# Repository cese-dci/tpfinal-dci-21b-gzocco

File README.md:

## Trabajo práctico final de la asignatura DCI ##
Este repositorio contiene el trabajo práctico final para la asignatura de Diseño de Circuitos Impresos de la carrera de posgrado de FIUBA.

* **Autor:** Gustavo Zocco
* **Revisor:** Agustín Curcio Berardi
* **Docente:** Diego Brengui
* **Título corto del trabajo:** Réplica Giroscopio L3GD20H.
* **Descripción:**  Réplica del módulo giroscopio de 3 ejes con el CI L3GD20H.

<p align="center">
    <br>
    <b>Figura 1</b>. Vista de frente de la placa adaptada. 
</p>

<p align="center">
    <br>
    <b>Figura 2</b>. Vista en perspectiva 3d de la placa adaptada. 
</p>

## Adaptaciones realizadas al replicar la placa ##

En este trabajo se realizaron adaptaciones sobre la placa propuesta a los efectos de satisfacer los requerimientos establecidos, como se detalla a cantinuación:

- Se agregó un tercer fiducial.
- Se agregaron las referencias a los componentes que no las tenían en el diseño original.
- Como consecuencia de documentar las referencias la placa tiene 21 mm de alto (2 mm más que la original) y 37 mm de ancho (6.5 mm más que la original).
- Se agregó plano de tierra de GND en la cara superior de la placa.

## Licencia de este trabajo ##
CERN Open Hardware License (OHL)
Ver la sección "What license should I use?": https://www.oshwa.org/faq/

## Estructura ##

El presente trabajo contempla la siguiente estructura.

* doc: Toda la información sobre el circuito.
  * Notas de aplicación.
  * Esquemático.
  * Fotos de los prototipos.
* info: Toda la iformación recolectada, principalmente de terceros, como por ejemplo:
  * Hojas de datos.
  * Notas de aplicación.
  * Info de productos comerciales.
  * Info en internet.
* pcb: Archivos de diseño esquemático y pcb.

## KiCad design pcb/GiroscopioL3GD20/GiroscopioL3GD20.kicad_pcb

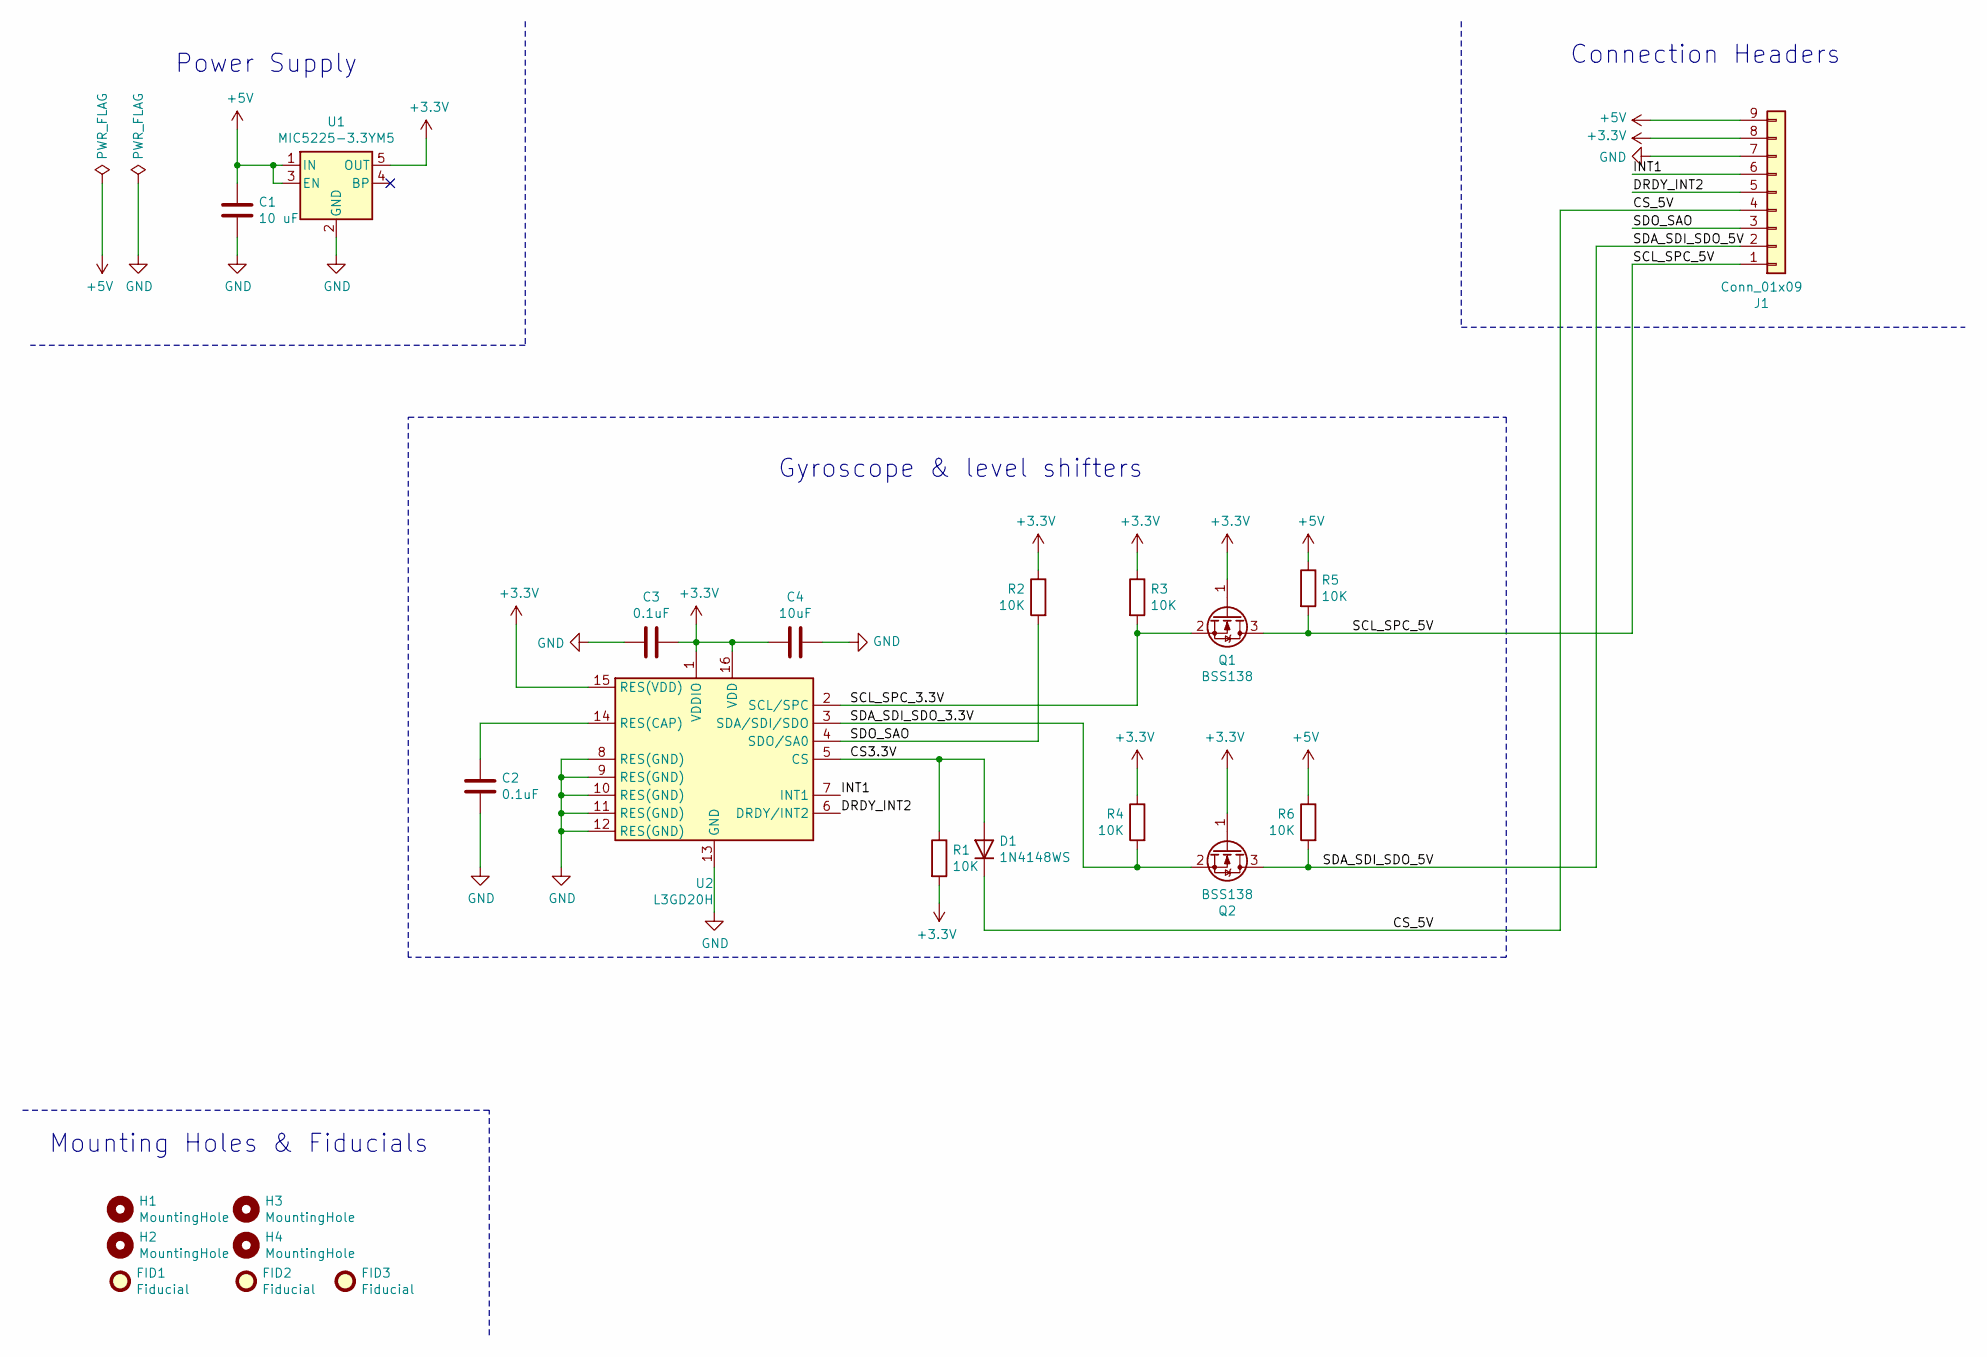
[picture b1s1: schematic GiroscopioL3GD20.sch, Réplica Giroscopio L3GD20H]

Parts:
C1: 10 uF; C_0805_2012Metric_Pad1.18x1.45mm_HandSolder
C2, C3: 0.1uF; C_0805_2012Metric_Pad1.18x1.45mm_HandSolder
C4: 10uF; C_0805_2012Metric_Pad1.18x1.45mm_HandSolder
D1: 1N4148WS; D_SOD-323
FID1, FID2, FID3: Fiducial; Fiducial_1mm_Mask2mm
H1, H2, H3, H4: MountingHole; MountingHole_2.5mm_Pad_TopBottom
J1: Conn_01x09; PinHeader_1x09_P2.54mm_Vertical
Q1: BSS138; SOT-23; Digi-Key PN BSS138-DIE-ND
Q2: BSS138; SOT-23; Digi-Key PN BSS138TR-ND
R1, R2, R3, R4, R5, R6: 10K; R_0805_2012Metric_Pad1.20x1.40mm_HandSolder
U1: MIC5225-3.3YM5; SOT-23-5; Digi-Key PN 576-2980-2-ND
U2: L3GD20H; LGA-16_3x3mm_P0.5mm; Digi-Key PN 497-13931-2-ND

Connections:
+3V3: C3.1, C4.2, J1.8, Q1.1 (G), Q2.1 (G), R1.2, R2.1, R3.1, R4.1, U1.5 (OUT), U2.1 (VDDIO), U2.15 (RES(VDD)), U2.16 (VDD)
+5V: C1.1, J1.9, R5.1, R6.1, U1.1 (IN), U1.3 (EN)
/CS3.3V: D1.2 (A), R1.1, U2.5 (CS)
/CS_5V: D1.1 (K), J1.4
/DRDY_INT2: J1.5, U2.6 (DRDY/INT2)
/INT1: J1.6, U2.7 (INT1)
/SCL_SPC_3.3V: Q1.2 (S), R3.2, U2.2 (SCL/SPC)
/SCL_SPC_5V: J1.1, Q1.3 (D), R5.2
/SDA_SDI_SDO_3.3V: Q2.2 (S), R4.2, U2.3 (SDA/SDI/SDO)
/SDA_SDI_SDO_5V: J1.2, Q2.3 (D), R6.2
/SDO_SAO: J1.3, R2.2, U2.4 (SDO/SA0)
GND: C1.2, C2.2, C3.2, C4.1, J1.7, U1.2 (GND), U2.8 (RES(GND)), U2.9 (RES(GND)), U2.10 (RES(GND)), U2.11 (RES(GND)), U2.12 (RES(GND)), U2.13 (GND)
unnamed: C2.1, U2.14 (RES(CAP))

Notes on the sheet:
Connection Headers
Mounting Holes & Fiducials
Gyroscope & level shifters
Power Supply

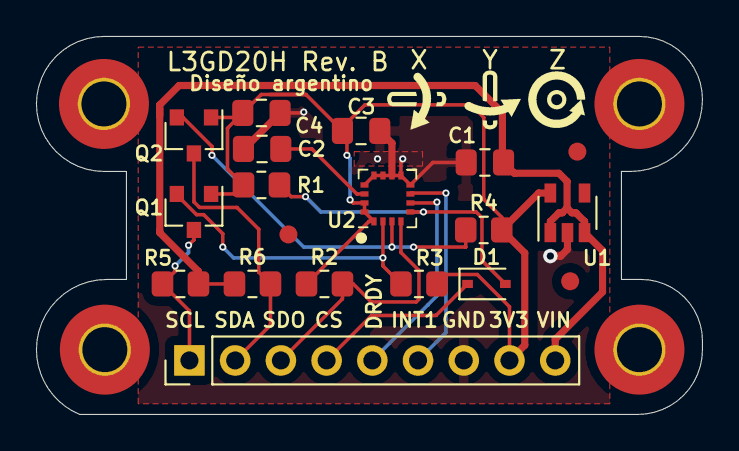
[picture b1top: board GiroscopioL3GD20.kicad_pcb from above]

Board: 2 copper layers, 37.0 x 21.0 mm, 24 parts (0 on the bottom side), 13 nets.

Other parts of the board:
U$3: SYMBOL_GYROXYZ_10MM

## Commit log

2021-07-01 Agrego: documentacion de componentes, nota de aplicacion y esquematico
2021-07-01 Se agrega esquematico en PDF
2021-07-01 Se realizan correcciones
2021-07-01 Se actualiza Esquematico.pdf conforme cambios realizados
2021-08-02 Se agrega Placement, borde de placa, notas de PCB, cotas y otros.
2021-08-02 Se agregó info a las notas del PCB
2021-08-12 Correcciones del esquematico y ruteo del PCB
2021-08-12 Actualización README
2021-08-16 Correcciones. Se agrega Fiducial. Se corrigen posiciones de serigrafias.
2021-08-16 Mejoras en rotulo y p tierra.
2021-08-16 Se agrega documentacion
